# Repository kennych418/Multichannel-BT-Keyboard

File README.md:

# Multichannel BT Keyboard
When someone has to work with multiple devices, whether it's a home computer, work laptop, or mobile tablet, they have to switch between multiple keyboards to type to each device. This is inconvenient for anyone who values their desk space or hates the soulcrushing burden of having to move your hands a couple degrees. The multichannel BT keyboard is designed to simplify transitions between devices by connecting to up to three different devices and changing the target with the press of a button. 

INSERT PHOTO HERE

## Schematic
The significant hardware decisions are listed below. 
* ATMega32u4 Microcontroller
* RN42 Bluetooth Module
* MIC4680 Voltage Regulator
* ______ Diodes

We chose to use the ATMega32u4 microcontroller because of its high number of GPIO pins and compatibility with the Arduino IDE. It provides just the right number of GPIO pins to act as inputs and outputs for 72 keys. The Arduino IDE simplifies the programming for the keyboard's firmware. Along with that, there is a lot of online support for Arduino devices and projects.

The RN42 bluetooth module .

## PCB
There are many ways to design a PCB and we won't be discussing design practices. The main priority behind our PCB design was to avoid bottlenecking high current components, like the microcontroller, bluetooth modules, voltage regulator, and batteries. Since the keyboard is primarily digital, the rest of the design simply aims to connect signals together with traces. 

## Files

## CAD Models

## RN42 First Time Setup
All commands are entered in command mode with a 10ms delay between each one. Exit command mode and save with **R,1\n**.  
Enable HID mode with **S~,6\n**.  
Enable authentication mode 0 with **SA,0\n**. Default pin is 1234.  
Configure the device name with **SN,`value`\n**, where value is an up to 20 character alphanumeric string.
Configure flag register with **SH,`value`\n**, where value is 4 hex characters. Set bits 0-3 high (020F).  
Enable auto-reconnect with **SM,6\n**.  

## Future Improvements
Set inactive RN42s into low power mode by controlling their RESET pin. Requires a new schematic and PCB design.  
Use the RN42 RX pin for easier debugging.
Add a voltage divider to check battery percentage and report it to the host device similar to Logitech's devices.
Use a microcontroller with more pins, possibly an STM.  
Add screw holes to case and PCB to improve rigidity and compatibility with standard consumer cases.

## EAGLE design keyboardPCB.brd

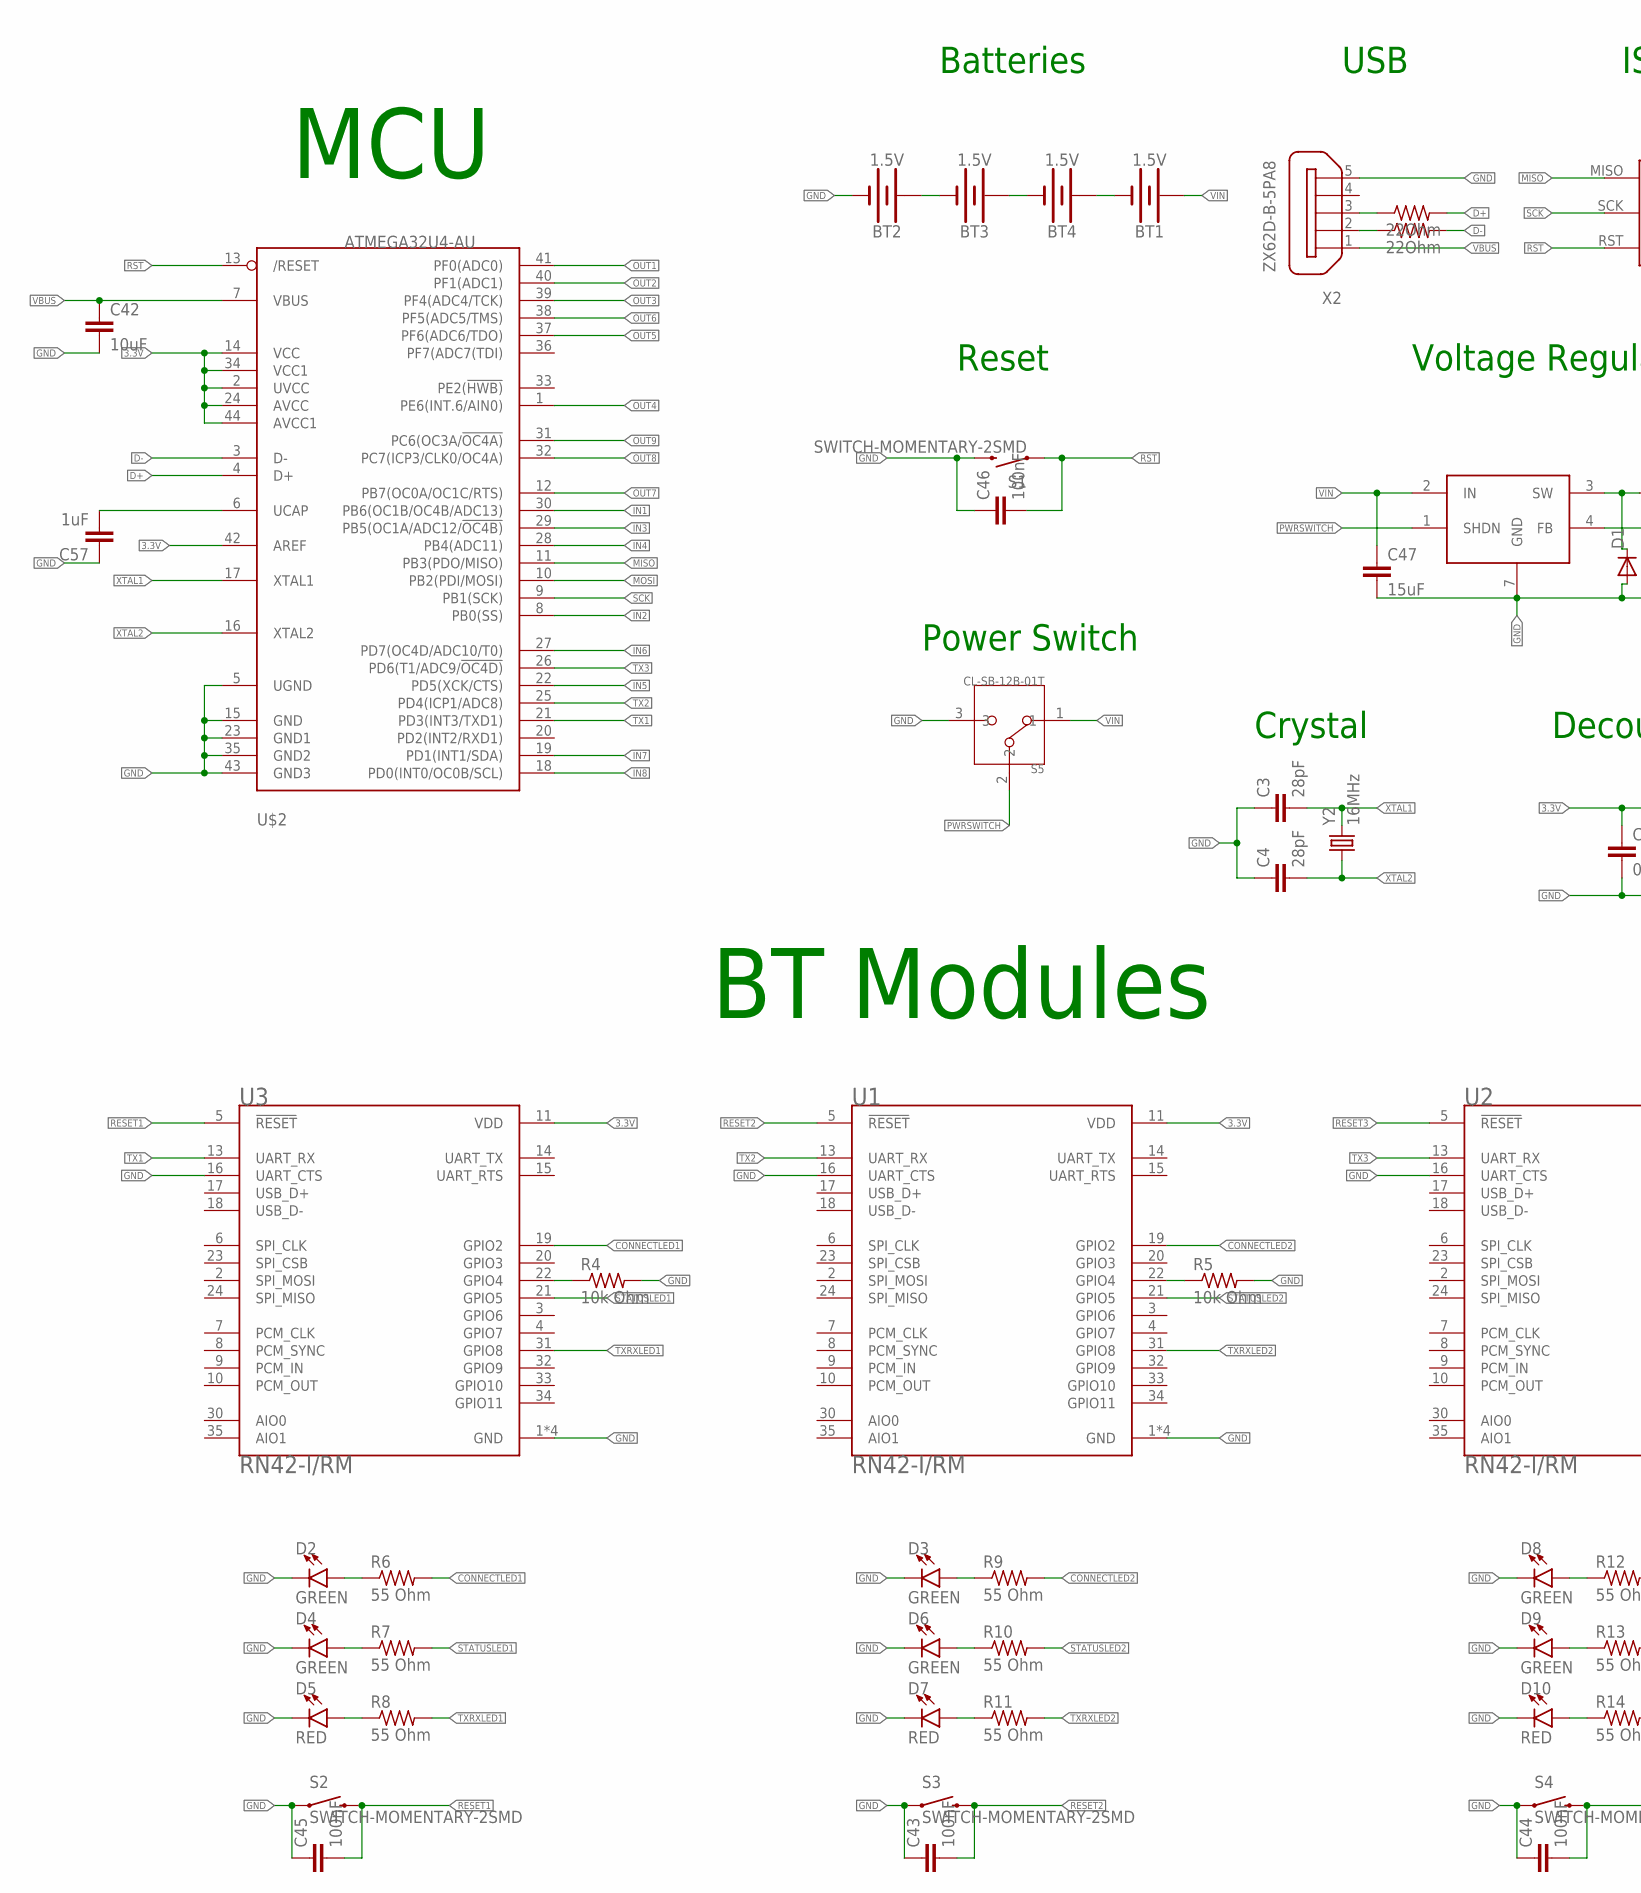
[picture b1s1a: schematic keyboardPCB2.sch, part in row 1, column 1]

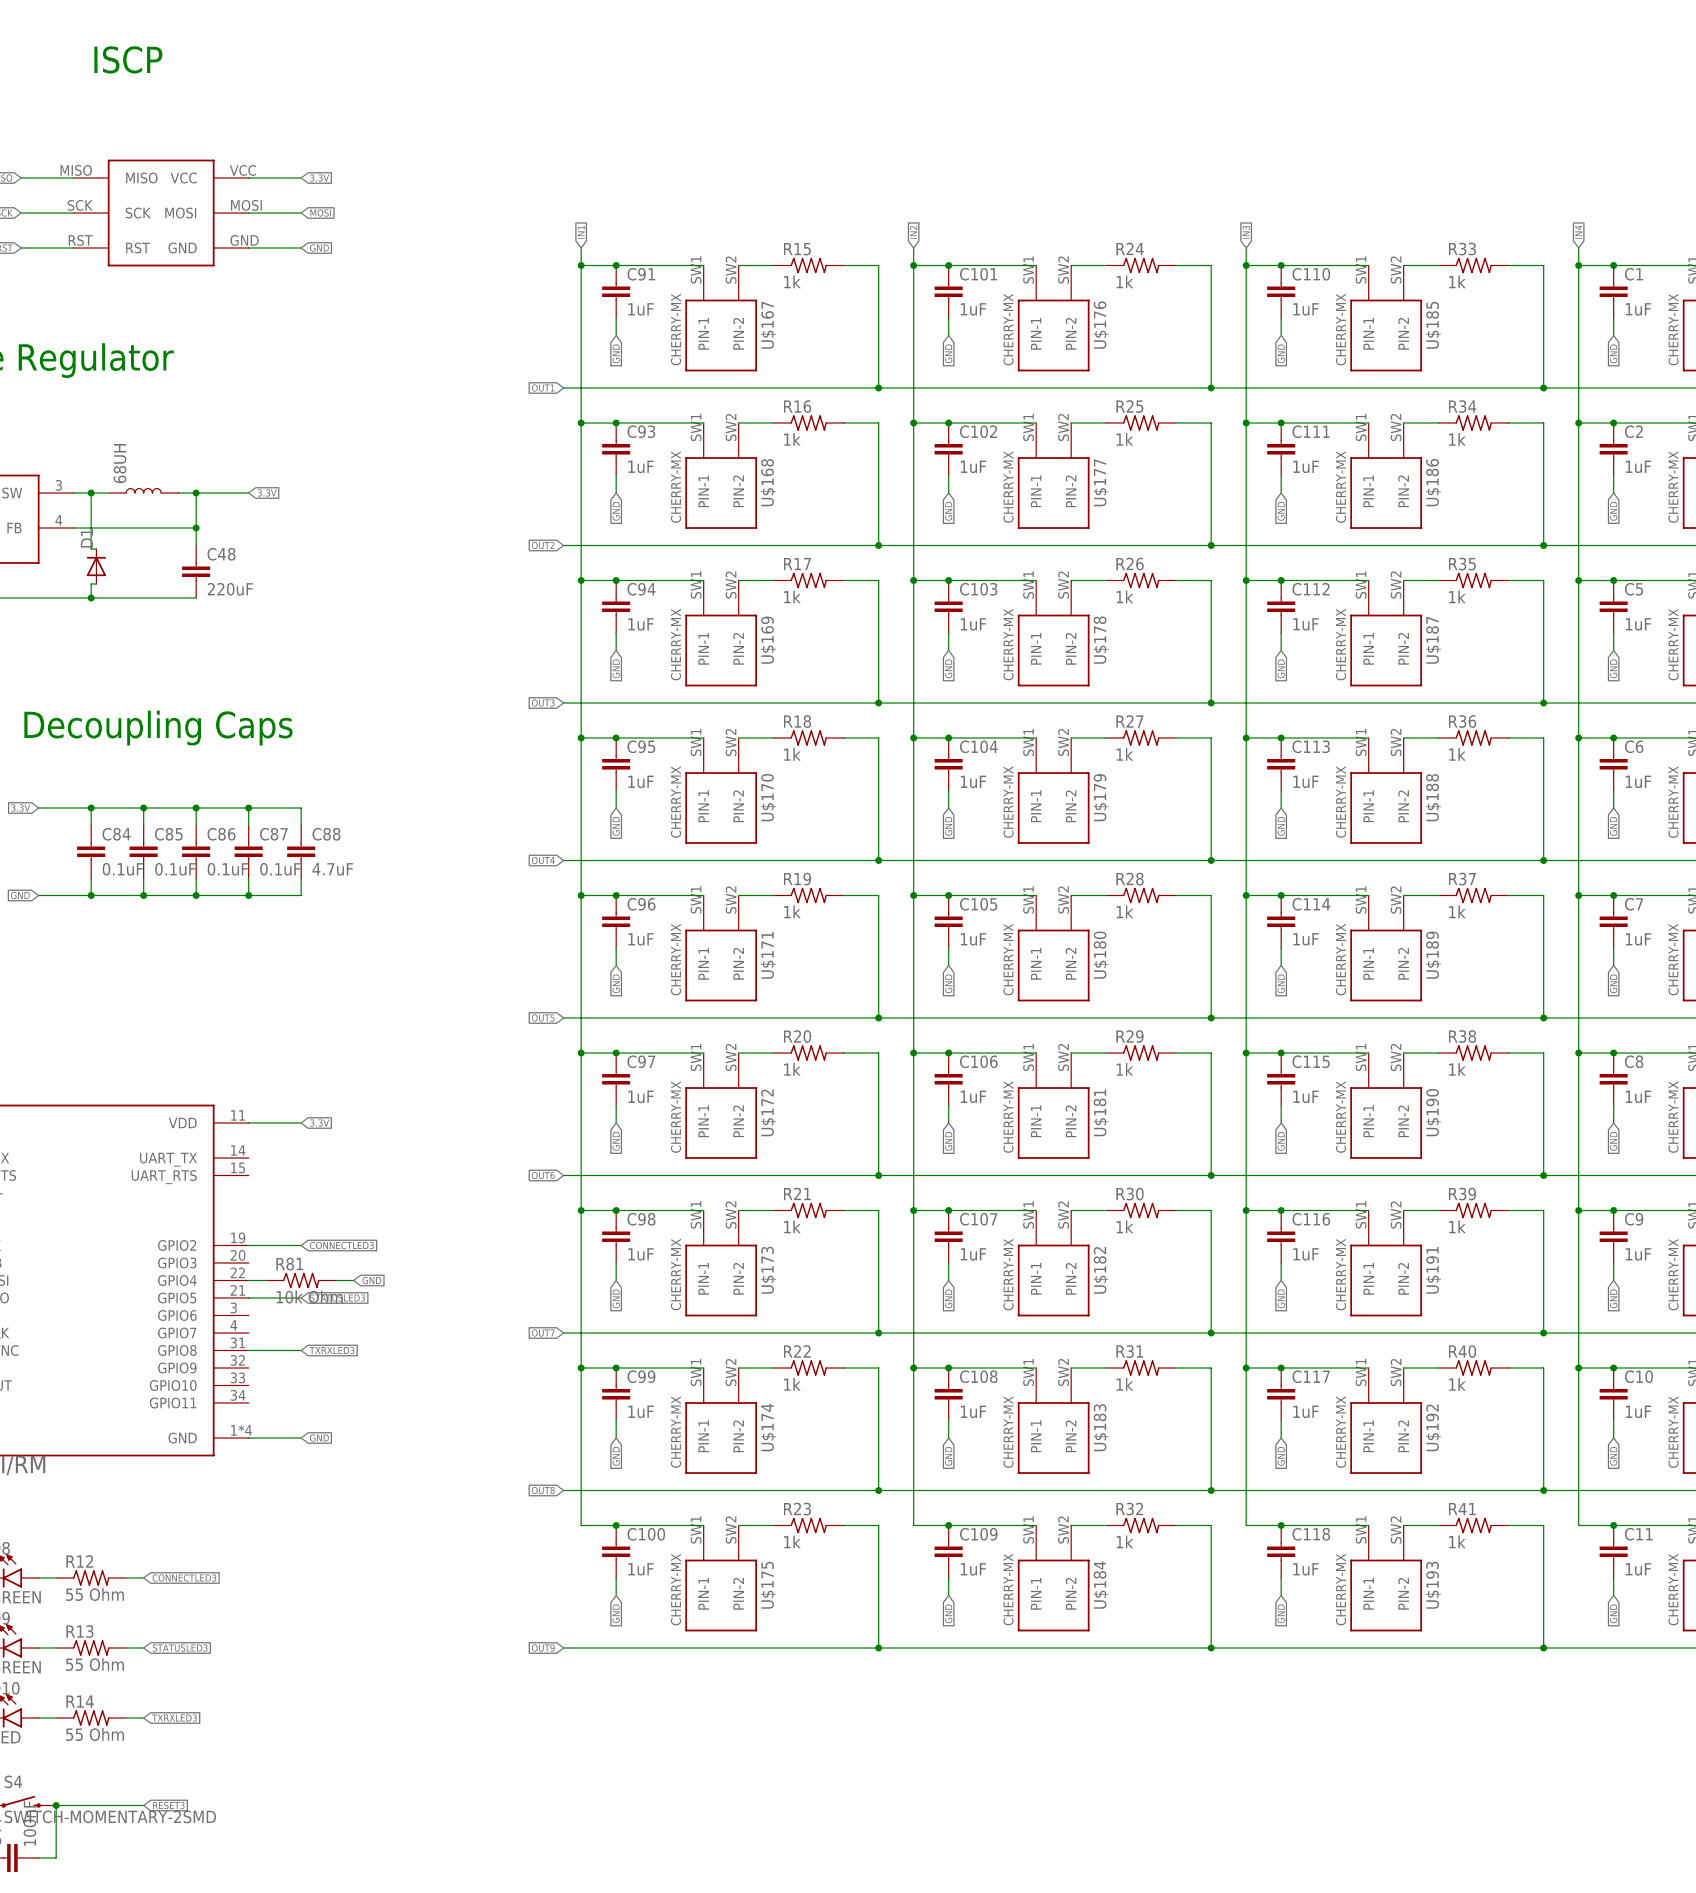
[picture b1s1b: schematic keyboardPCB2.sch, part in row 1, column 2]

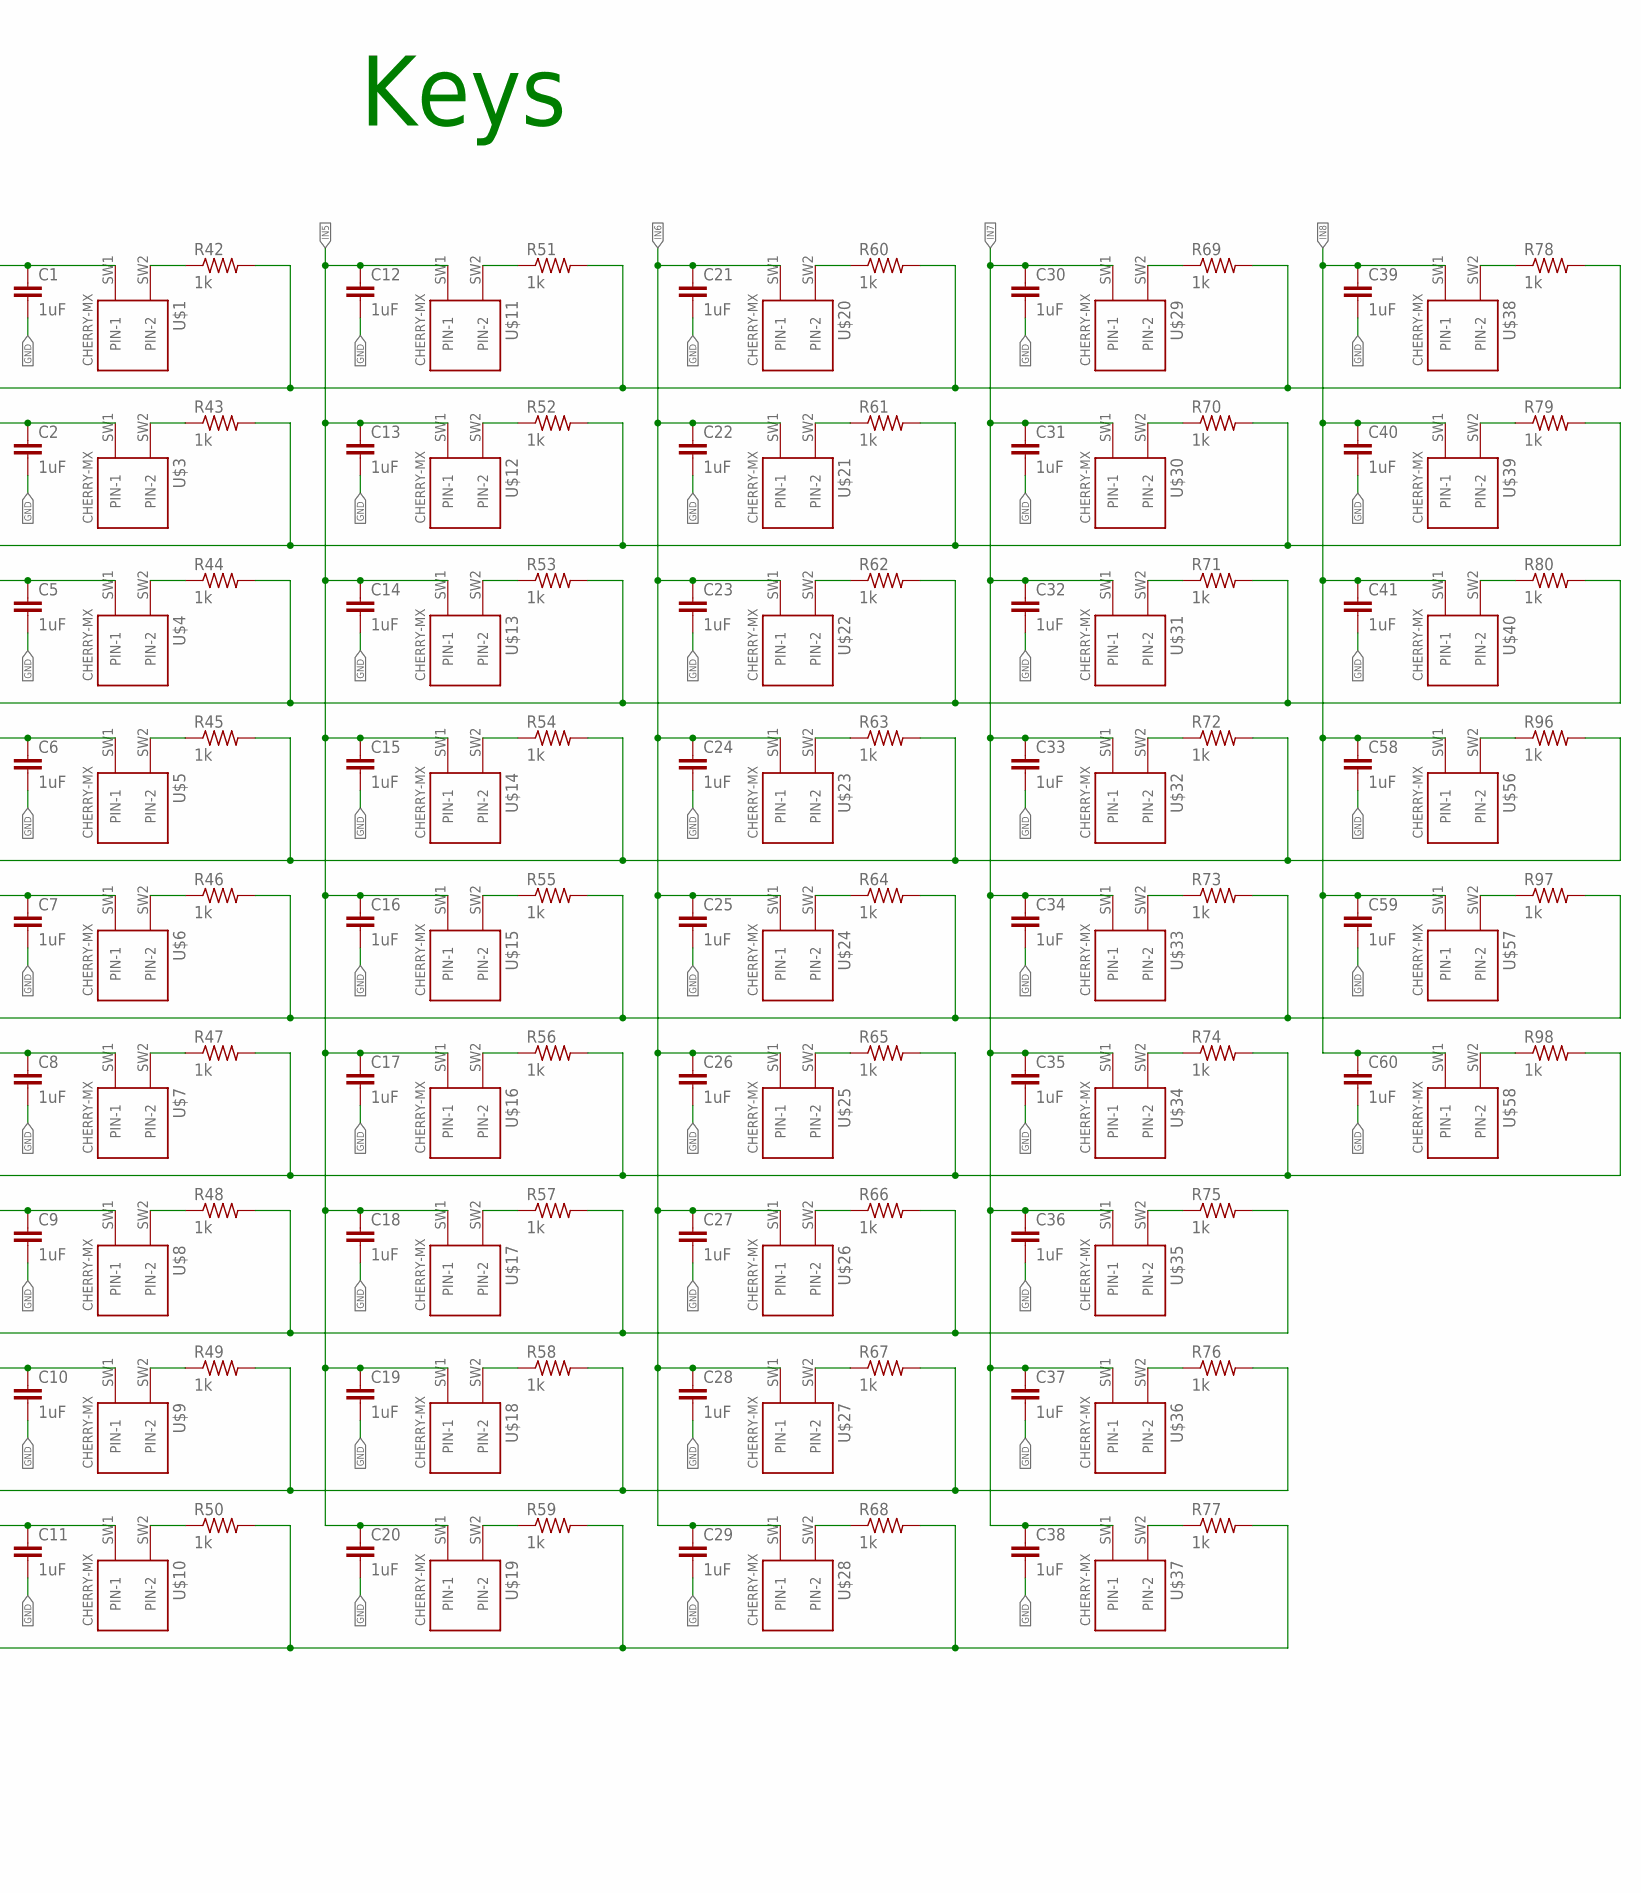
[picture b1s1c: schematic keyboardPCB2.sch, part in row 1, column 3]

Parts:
68UH: 33nH/±5%/500mA; 0603
BT1, BT2, BT3, BT4: 1.5V; BATTERY-AA
C1, C2, C5, C6, C7, C8, C9, C10, C11, C12, C13, C14, C15, C16, C17, C18, C19, C20, C21, C22, C23, C24, C25, C26, C27, C28, C29, C30, C31, C32, C33, C34, C35, C36, C37, C38, C39, C40, C41, C57, C58, C59, C60, C91, C93, C94, C95, C96, C97, C98, C99, C100, C101, C102, C103, C104, C105, C106, C107, C108, C109, C110, C111, C112, C113, C114, C115, C116, C117, C118: 1uF; C0402K
C3, C4: 28pF; C0402K
C42: 10uF; C0402K
C43, C44, C45, C46: 100nF; C0402K
C47: 15uF; C0603K
C48: 220uF; C1206
C84, C85, C86, C87: 0.1uF; C0402K
C88: 4.7uF; C0402K
D1: S2A; DO214AA
D2, D3, D4, D6, D8, D9: GREEN; LED-0603
D5, D7, D10: RED; LED-0603
R2, R3: 22Ohm; R0402
R4, R5, R81: 10k Ohm; R0402
R6, R7, R8, R9, R10, R11, R12, R13, R14: 55 Ohm; R0402
R15, R16, R17, R18, R19, R20, R21, R22, R23, R24, R25, R26, R27, R28, R29, R30, R31, R32, R33, R34, R35, R36, R37, R38, R39, R40, R41, R42, R43, R44, R45, R46, R47, R48, R49, R50, R51, R52, R53, R54, R55, R56, R57, R58, R59, R60, R61, R62, R63, R64, R65, R66, R67, R68, R69, R70, R71, R72, R73, R74, R75, R76, R77, R78, R79, R80, R96, R97, R98: 1k; R0402
S1, S2, S3, S4: SWITCH-MOMENTARY-2SMD; TACTILE-SWITCH-SMD
S5: CL-SB-12B-01T; CL-SB-12B
U1, U2, U3: RN42-I/RM; XCVR_RN42-I/RM
U$1, U$3, U$4, U$5, U$6, U$7, U$8, U$9, U$10, U$11, U$12, U$13, U$14, U$15, U$16, U$17, U$18, U$19, U$20, U$21, U$22, U$23, U$24, U$25, U$26, U$27, U$28, U$29, U$30, U$31, U$32, U$33, U$34, U$35, U$36, U$37, U$38, U$39, U$40, U$56, U$57, U$58, U$167, U$168, U$169, U$170, U$171, U$172, U$173, U$174, U$175, U$176, U$177, U$178, U$179, U$180, U$181, U$182, U$183, U$184, U$185, U$186, U$187, U$188, U$189, U$190, U$191, U$192, U$193: CHERRY-MX
U$2: ATMEGA32U4-AU; TQFP44
U$59: AVR-ISP
U$166: MIC4680; SOIC-8
X2: ZX62D-B-5PA8
Y2: 16MHz; HC49UP

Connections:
3.3V: 68UH.2, C48.1, C84.1, C85.1, C86.1, C87.1, C88.1, U1.11 (VDD), U2.11 (VDD), U3.11 (VDD), U$2.2 (UVCC), U$2.14 (VCC), U$2.24 (AVCC), U$2.34 (VCC1), U$2.42 (AREF), U$2.44 (AVCC1), U$59.VCC, U$166.4 (FB)
CONNECTLED1: R6.2, U3.19 (GPIO2)
CONNECTLED2: R9.2, U1.19 (GPIO2)
CONNECTLED3: R12.2, U2.19 (GPIO2)
D+: R2.2, U$2.4 (D+)
D-: R3.2, U$2.3 (D-)
GND: BT2.GND@1 (-), C1.2, C2.2, C3.1, C4.1, C5.2, C6.2, C7.2, C8.2, C9.2, C10.2, C11.2, C12.2, C13.2, C14.2, C15.2, C16.2, C17.2, C18.2, C19.2, C20.2, C21.2, C22.2, C23.2, C24.2, C25.2, C26.2, C27.2, C28.2, C29.2, C30.2, C31.2, C32.2, C33.2, C34.2, C35.2, C36.2, C37.2, C38.2, C39.2, C40.2, C41.2, C42.2, C43.1, C44.1, C45.1, C46.1, C47.2, C48.2, C57.1, C58.2, C59.2, C60.2, C84.2, C85.2, C86.2, C87.2, C88.2, C91.2, C93.2, C94.2, C95.2, C96.2, C97.2, C98.2, C99.2, C100.2, C101.2, C102.2, C103.2, C104.2, C105.2, C106.2, C107.2, C108.2, C109.2, C110.2, C111.2, C112.2, C113.2, C114.2, C115.2, C116.2, C117.2, C118.2, D1.A, D2.C, D3.C, D4.C, D5.C, D6.C, D7.C, D8.C, D9.C, D10.C, R4.2, R5.2, R81.2, S1.3 (2), S2.1, S3.1, S4.1, S5.3, U1.1 (GND), U1.12 (GND), U1.16 (UART_CTS), U1.28 (GND), U1.29 (GND), U2.1 (GND), U2.12 (GND), U2.16 (UART_CTS), U2.28 (GND), U2.29 (GND), U3.1 (GND), U3.12 (GND), U3.16 (UART_CTS), U3.28 (GND), U3.29 (GND), U$2.5 (UGND), U$2.15 (GND), U$2.23 (GND1), U$2.35 (GND2), U$2.43 (GND3), U$59.GND, U$166.5 (GND), U$166.6 (GND), U$166.7 (GND), U$166.8 (GND), X2.5
IN1: C91.1, C93.1, C94.1, C95.1, C96.1, C97.1, C98.1, C99.1, C100.1, U$2.30 (PB6(OC1B/OC4B/ADC13)), U$167.SW1 (PIN-1), U$168.SW1 (PIN-1), U$169.SW1 (PIN-1), U$170.SW1 (PIN-1), U$171.SW1 (PIN-1), U$172.SW1 (PIN-1), U$173.SW1 (PIN-1), U$174.SW1 (PIN-1), U$175.SW1 (PIN-1)
IN2: C101.1, C102.1, C103.1, C104.1, C105.1, C106.1, C107.1, C108.1, C109.1, U$2.8 (PB0(SS)), U$176.SW1 (PIN-1), U$177.SW1 (PIN-1), U$178.SW1 (PIN-1), U$179.SW1 (PIN-1), U$180.SW1 (PIN-1), U$181.SW1 (PIN-1), U$182.SW1 (PIN-1), U$183.SW1 (PIN-1), U$184.SW1 (PIN-1)
IN3: C110.1, C111.1, C112.1, C113.1, C114.1, C115.1, C116.1, C117.1, C118.1, U$2.29 (PB5(OC1A/ADC12/!OC4B)), U$185.SW1 (PIN-1), U$186.SW1 (PIN-1), U$187.SW1 (PIN-1), U$188.SW1 (PIN-1), U$189.SW1 (PIN-1), U$190.SW1 (PIN-1), U$191.SW1 (PIN-1), U$192.SW1 (PIN-1), U$193.SW1 (PIN-1)
IN4: C1.1, C2.1, C5.1, C6.1, C7.1, C8.1, C9.1, C10.1, C11.1, U$1.SW1 (PIN-1), U$2.28 (PB4(ADC11)), U$3.SW1 (PIN-1), U$4.SW1 (PIN-1), U$5.SW1 (PIN-1), U$6.SW1 (PIN-1), U$7.SW1 (PIN-1), U$8.SW1 (PIN-1), U$9.SW1 (PIN-1), U$10.SW1 (PIN-1)
IN5: C12.1, C13.1, C14.1, C15.1, C16.1, C17.1, C18.1, C19.1, C20.1, U$2.22 (PD5(XCK/CTS)), U$11.SW1 (PIN-1), U$12.SW1 (PIN-1), U$13.SW1 (PIN-1), U$14.SW1 (PIN-1), U$15.SW1 (PIN-1), U$16.SW1 (PIN-1), U$17.SW1 (PIN-1), U$18.SW1 (PIN-1), U$19.SW1 (PIN-1)
IN6: C21.1, C22.1, C23.1, C24.1, C25.1, C26.1, C27.1, C28.1, C29.1, U$2.27 (PD7(OC4D/ADC10/T0)), U$20.SW1 (PIN-1), U$21.SW1 (PIN-1), U$22.SW1 (PIN-1), U$23.SW1 (PIN-1), U$24.SW1 (PIN-1), U$25.SW1 (PIN-1), U$26.SW1 (PIN-1), U$27.SW1 (PIN-1), U$28.SW1 (PIN-1)
IN7: C30.1, C31.1, C32.1, C33.1, C34.1, C35.1, C36.1, C37.1, C38.1, U$2.19 (PD1(INT1/SDA)), U$29.SW1 (PIN-1), U$30.SW1 (PIN-1), U$31.SW1 (PIN-1), U$32.SW1 (PIN-1), U$33.SW1 (PIN-1), U$34.SW1 (PIN-1), U$35.SW1 (PIN-1), U$36.SW1 (PIN-1), U$37.SW1 (PIN-1)
IN8: C39.1, C40.1, C41.1, C58.1, C59.1, C60.1, U$2.18 (PD0(INT0/OC0B/SCL)), U$38.SW1 (PIN-1), U$39.SW1 (PIN-1), U$40.SW1 (PIN-1), U$56.SW1 (PIN-1), U$57.SW1 (PIN-1), U$58.SW1 (PIN-1)
MISO: U$2.11 (PB3(PDO/MISO)), U$59.MISO
MOSI: U$2.10 (PB2(PDI/MOSI)), U$59.MOSI
unnamed: R42.1, U$1.SW2 (PIN-2)
unnamed: BT2.PWR@1 (+), BT3.GND@1 (-)
unnamed: C57.2, U$2.6 (UCAP)
unnamed: BT3.PWR@1 (+), BT4.GND@1 (-)
unnamed: R96.1, U$56.SW2 (PIN-2)
unnamed: R43.1, U$3.SW2 (PIN-2)
unnamed: R4.1, U3.22 (GPIO4)
unnamed: R97.1, U$57.SW2 (PIN-2)
unnamed: D2.A, R6.1
unnamed: D4.A, R7.1
unnamed: R44.1, U$4.SW2 (PIN-2)
unnamed: R98.1, U$58.SW2 (PIN-2)
unnamed: BT1.GND@1 (-), BT4.PWR@1 (+)
unnamed: R45.1, U$5.SW2 (PIN-2)
unnamed: D5.A, R8.1
unnamed: 68UH.1, D1.C, U$166.3 (SW)
unnamed: R46.1, U$6.SW2 (PIN-2)
unnamed: R47.1, U$7.SW2 (PIN-2)
unnamed: D3.A, R9.1
unnamed: D6.A, R10.1
unnamed: D7.A, R11.1
unnamed: D8.A, R12.1
unnamed: R48.1, U$8.SW2 (PIN-2)
unnamed: D9.A, R13.1
unnamed: R5.1, U1.22 (GPIO4)
unnamed: R49.1, U$9.SW2 (PIN-2)
unnamed: D10.A, R14.1
unnamed: R50.1, U$10.SW2 (PIN-2)
unnamed: R2.1, X2.3
unnamed: R51.1, U$11.SW2 (PIN-2)
unnamed: R52.1, U$12.SW2 (PIN-2)
unnamed: R53.1, U$13.SW2 (PIN-2)
unnamed: R54.1, U$14.SW2 (PIN-2)
unnamed: R24.1, U$176.SW2 (PIN-2)
unnamed: R55.1, U$15.SW2 (PIN-2)
unnamed: R15.1, U$167.SW2 (PIN-2)
unnamed: R56.1, U$16.SW2 (PIN-2)
unnamed: R57.1, U$17.SW2 (PIN-2)
unnamed: R58.1, U$18.SW2 (PIN-2)
unnamed: R3.1, X2.2
unnamed: R59.1, U$19.SW2 (PIN-2)
unnamed: R60.1, U$20.SW2 (PIN-2)
unnamed: R61.1, U$21.SW2 (PIN-2)
unnamed: R62.1, U$22.SW2 (PIN-2)
unnamed: R63.1, U$23.SW2 (PIN-2)
unnamed: R64.1, U$24.SW2 (PIN-2)
unnamed: R65.1, U$25.SW2 (PIN-2)
unnamed: R66.1, U$26.SW2 (PIN-2)
unnamed: R67.1, U$27.SW2 (PIN-2)
unnamed: R16.1, U$168.SW2 (PIN-2)
unnamed: R68.1, U$28.SW2 (PIN-2)
unnamed: R69.1, U$29.SW2 (PIN-2)
unnamed: R81.1, U2.22 (GPIO4)
unnamed: R25.1, U$177.SW2 (PIN-2)
unnamed: R70.1, U$30.SW2 (PIN-2)
unnamed: R71.1, U$31.SW2 (PIN-2)
unnamed: R72.1, U$32.SW2 (PIN-2)
unnamed: R73.1, U$33.SW2 (PIN-2)
unnamed: R17.1, U$169.SW2 (PIN-2)
unnamed: R74.1, U$34.SW2 (PIN-2)
unnamed: R75.1, U$35.SW2 (PIN-2)
unnamed: R76.1, U$36.SW2 (PIN-2)
unnamed: R77.1, U$37.SW2 (PIN-2)
unnamed: R78.1, U$38.SW2 (PIN-2)
unnamed: R79.1, U$39.SW2 (PIN-2)
unnamed: R80.1, U$40.SW2 (PIN-2)
unnamed: R18.1, U$170.SW2 (PIN-2)
unnamed: R26.1, U$178.SW2 (PIN-2)
unnamed: R19.1, U$171.SW2 (PIN-2)
unnamed: R20.1, U$172.SW2 (PIN-2)
unnamed: R27.1, U$179.SW2 (PIN-2)
unnamed: R21.1, U$173.SW2 (PIN-2)
unnamed: R22.1, U$174.SW2 (PIN-2)
unnamed: R28.1, U$180.SW2 (PIN-2)
unnamed: R23.1, U$175.SW2 (PIN-2)
unnamed: R29.1, U$181.SW2 (PIN-2)
unnamed: R30.1, U$182.SW2 (PIN-2)
unnamed: R31.1, U$183.SW2 (PIN-2)
unnamed: R32.1, U$184.SW2 (PIN-2)
unnamed: R33.1, U$185.SW2 (PIN-2)
unnamed: R34.1, U$186.SW2 (PIN-2)
unnamed: R35.1, U$187.SW2 (PIN-2)
unnamed: R36.1, U$188.SW2 (PIN-2)
unnamed: R37.1, U$189.SW2 (PIN-2)
unnamed: R38.1, U$190.SW2 (PIN-2)
unnamed: R39.1, U$191.SW2 (PIN-2)
unnamed: R40.1, U$192.SW2 (PIN-2)
unnamed: R41.1, U$193.SW2 (PIN-2)
OUT1: R15.2, R24.2, R33.2, R42.2, R51.2, R60.2, R69.2, R78.2, U$2.41 (PF0(ADC0))
OUT2: R16.2, R25.2, R34.2, R43.2, R52.2, R61.2, R70.2, R79.2, U$2.40 (PF1(ADC1))
OUT3: R17.2, R26.2, R35.2, R44.2, R53.2, R62.2, R71.2, R80.2, U$2.39 (PF4(ADC4/TCK))
OUT4: R18.2, R27.2, R36.2, R45.2, R54.2, R63.2, R72.2, R96.2, U$2.1 (PE6(INT.6/AIN0))
OUT5: R19.2, R28.2, R37.2, R46.2, R55.2, R64.2, R73.2, R97.2, U$2.37 (PF6(ADC6/TDO))
OUT6: R20.2, R29.2, R38.2, R47.2, R56.2, R65.2, R74.2, R98.2, U$2.38 (PF5(ADC5/TMS))
OUT7: R21.2, R30.2, R39.2, R48.2, R57.2, R66.2, R75.2, U$2.12 (PB7(OC0A/OC1C/RTS))
OUT8: R22.2, R31.2, R40.2, R49.2, R58.2, R67.2, R76.2, U$2.32 (PC7(ICP3/CLK0/OC4A))
OUT9: R23.2, R32.2, R41.2, R50.2, R59.2, R68.2, R77.2, U$2.31 (PC6(OC3A/!OC4A))
PWRSWITCH: S5.2, U$166.1 (SHDN)
RESET1: C45.2, S2.3 (2), U3.5 (!RESET)
RESET2: C43.2, S3.3 (2), U1.5 (!RESET)
RESET3: C44.2, S4.3 (2), U2.5 (!RESET)
RST: C46.2, S1.1, U$2.13 (/RESET), U$59.RST
SCK: U$2.9 (PB1(SCK)), U$59.SCK
STATUSLED1: R7.2, U3.21 (GPIO5)
STATUSLED2: R10.2, U1.21 (GPIO5)
STATUSLED3: R13.2, U2.21 (GPIO5)
TX1: U3.13 (UART_RX), U$2.21 (PD3(INT3/TXD1))
TX2: U1.13 (UART_RX), U$2.25 (PD4(ICP1/ADC8))
TX3: U2.13 (UART_RX), U$2.26 (PD6(T1/ADC9/!OC4D))
TXRXLED1: R8.2, U3.31 (GPIO8)
TXRXLED2: R11.2, U1.31 (GPIO8)
TXRXLED3: R14.2, U2.31 (GPIO8)
VBUS: C42.1, U$2.7 (VBUS), X2.1
VIN: BT1.PWR@1 (+), C47.1, S5.1, U$166.2 (IN)
XTAL1: C3.2, U$2.17 (XTAL1), Y2.2
XTAL2: C4.2, U$2.16 (XTAL2), Y2.1

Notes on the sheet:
Keys
MCU
BT Modules
Voltage Regulator
Batteries
USB
ISCP
Crystal
Decoupling Caps
Reset
Power Switch

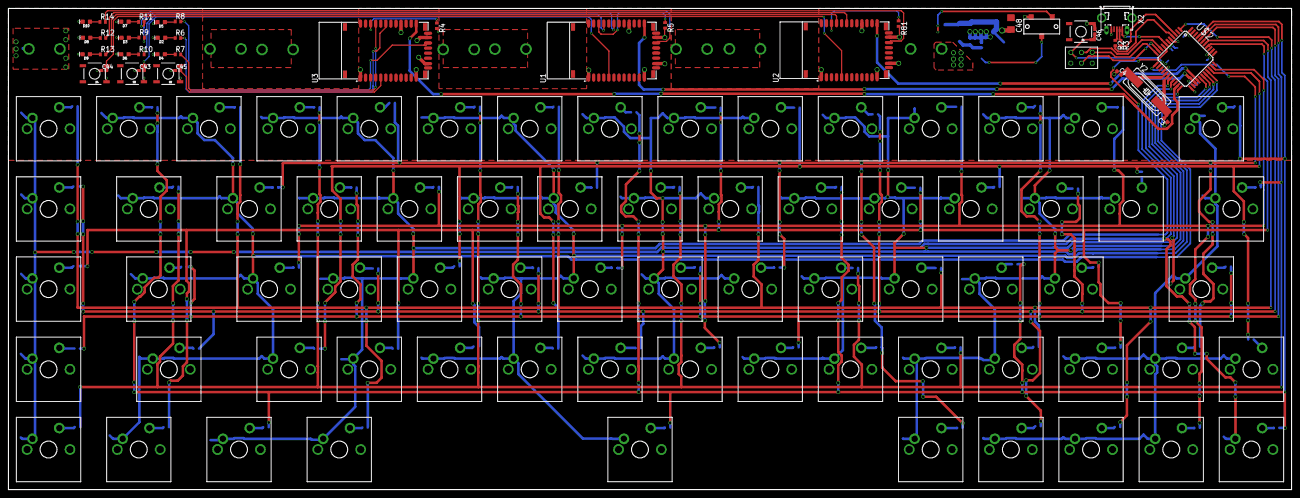
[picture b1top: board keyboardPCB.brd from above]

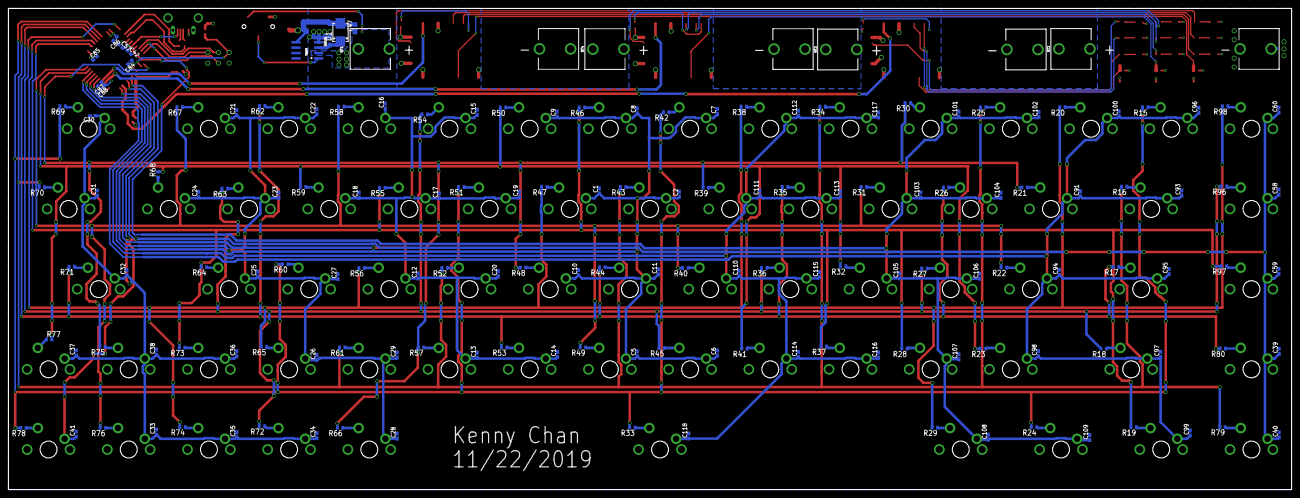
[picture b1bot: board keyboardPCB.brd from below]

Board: 2 copper layers, 304.0 x 114.0 mm, 264 parts (153 on the bottom side), 133 nets.

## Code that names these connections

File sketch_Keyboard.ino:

#include <Keyboard.h>
#include <SoftwareSerial.h>  

#define bluetooth1Rx 1
#define bluetooth2Rx 4
#define bluetooth3Rx 12

#define IN1 10
#define IN2 (1 << 0)  //Arduino IDE doesnt let me use PB0 >:(
#define IN3 9
#define IN4 8
#define IN5 (1 << 5)  //Arduino IDE doesnt let me use PD5 >:(
#define IN6 6
#define IN7 2
#define IN8 3

#define OUT1 A5
#define OUT2 A4
#define OUT3 A3
#define OUT4 7
#define OUT5 A1
#define OUT6 A2
#define OUT7 11
#define OUT8 13
#define OUT9 5

int pressedButtons[8] = {0};
uint8_t pressedKeys[6] = {0};
uint8_t keys[6] = {0x00};
uint8_t modifier = 0x00;

SoftwareSerial bluetooth1(NULL, bluetooth1Rx);
SoftwareSerial bluetooth2(NULL, bluetooth2Rx);
SoftwareSerial bluetooth3(NULL, bluetooth3Rx);

void setup()
{
  Keyboard.begin();
  Serial.begin(9600);

  pinMode(IN1, INPUT);
  pinMode(IN3, INPUT);
  pinMode(IN4, INPUT);
  pinMode(IN6, INPUT);
  pinMode(IN7, INPUT);
  pinMode(IN8, INPUT);

  //turn on internal pull ups
  digitalWrite(IN1, HIGH);
  digitalWrite(IN3, HIGH);
  digitalWrite(IN4, HIGH);
  digitalWrite(IN6, HIGH);
  digitalWrite(IN7, HIGH);
  digitalWrite(IN8, HIGH);

  //Set IN2 and IN5 as input pin with internal pull up
  DDRD &= ~IN5;
  PORTD |= IN5;
  DDRB &= ~IN2;
  PORTB |= IN2;
  
  pinMode(OUT1, OUTPUT);
  pinMode(OUT2, OUTPUT);
  pinMode(OUT3, OUTPUT);
  pinMode(OUT4, OUTPUT);
  pinMode(OUT5, OUTPUT);
  pinMode(OUT6, OUTPUT);
  pinMode(OUT7, OUTPUT);
  pinMode(OUT8, OUTPUT);
  pinMode(OUT9, OUTPUT);
  
  bluetooth1.begin(115200);  // The Bluetooth Mate defaults to 115200bps
  bluetooth2.begin(115200);  // The Bluetooth Mate defaults to 115200bps
  bluetooth3.begin(115200);  // The Bluetooth Mate defaults to 115200bps

  bluetooth1.print("$");  // Print three times individually
  bluetooth1.print("$");
  bluetooth1.print("$");  // Enter command mode
  delay(100);
  bluetooth1.print("S~,6\n");  // Enter enable HID
  delay(100);
  bluetooth1.print("R,1\n");   // Restart with HID
  delay(100);

  bluetooth2.print("$");  // Print three times individually
  bluetooth2.print("$");
  bluetooth2.print("$");  // Enter command mode
  delay(100);
  bluetooth2.print("S~,6\n");  // Enter enable HID
  delay(100);
  bluetooth2.print("R,1\n");   // Restart with HID
  delay(100);

  bluetooth3.print("$");  // Print three times individually
  bluetooth3.print("$");
  bluetooth3.print("$");  // Enter command mode
  delay(100);
  bluetooth3.print("S~,6\n");  // Enter enable HID
  delay(100);
  bluetooth3.print("R,1\n");   // Restart with HID
  delay(100);
}

void loop()
{
  int numPressed = 0;
  
  PORTB |= IN2;
  readKeys(1, pressedButtons);

  if(pressedButtons[0] == 0){
    pressedKeys[0] = 0x04;
    sendReport(pressedKeys, 0x00);
  }
  else{
    pressedKeys[0] = 0x00;
    sendReport(pressedKeys, 0x00);
  }
  /*PORTB |= IN2;
  readKeys(2, pressedButtons);
  PORTB |= IN2;
  readKeys(3, pressedButtons);
  PORTB |= IN2;
  readKeys(4, pressedButtons);
  PORTB |= IN2;
  readKeys(5, pressedButtons);
  PORTB |= IN2;
  readKeys(6, pressedButtons);
  PORTB |= IN2;
  readKeys(7, pressedButtons);
  PORTB |= IN2;
  readKeys(8, pressedButtons);
  PORTB |= IN2;
  readKeys(9, pressedButtons);*/
}

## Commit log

2020-02-17 Adding PCB and Code Files
2020-08-09 Working
2020-08-13 Added meta key
2020-08-15 Add low power optimizations
2020-10-16 README update 10/16

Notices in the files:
parts and their libraries:
SparkFun-Batteries: Licensing: Creative Commons ShareAlike 4.0 International - https://creativecommons.org/licenses/by-sa/4.0
